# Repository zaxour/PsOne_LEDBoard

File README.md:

# PsOne_LEDBoard
Simple switch board for PsOne LCD LED mods. 

Connects 4 LED's in a 2x2 configuration (2 parallel sets of 2 diodes in series) to the main board's 7.5V rail, which is then controlled by the AV port 5V supply, so that it only turns on when you press the power button on the system.

Parts are indicated on the schematic PDF - BJT gate resistors are 0603 size and the collector resistor is 1210/1206. The LED's I used are also indicated, but are ultimately up to the user. Just make sure to account for diode voltage drop and resize your resistor accordingly.

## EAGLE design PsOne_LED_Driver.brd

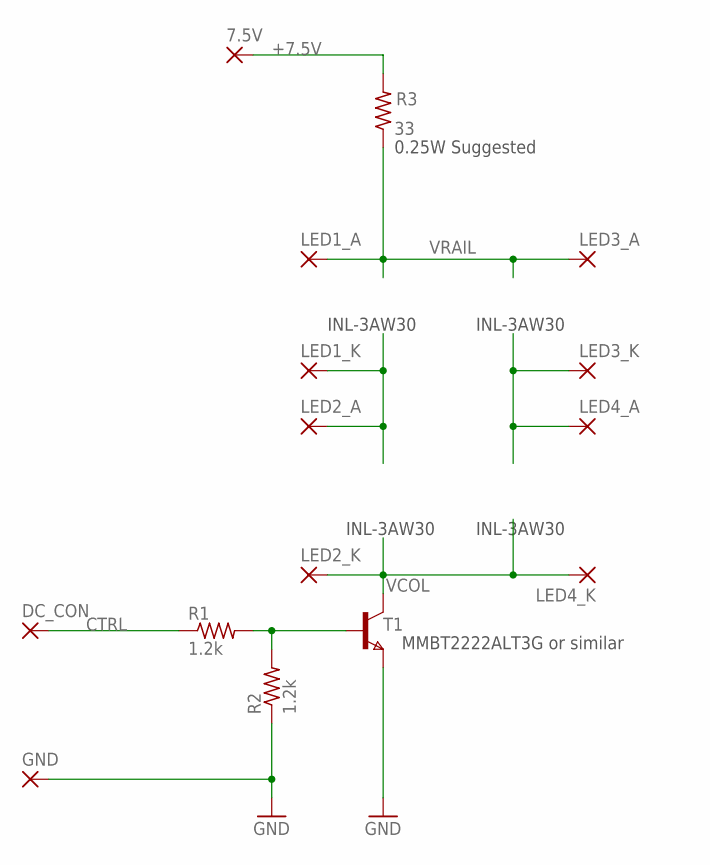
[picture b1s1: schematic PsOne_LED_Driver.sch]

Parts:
7.5V: SMD5; SMD2,54-5,08
DC_CON: SMD5; SMD2,54-5,08
GND: SMD5; SMD2,54-5,08
LED1_A, LED1_K, LED2_A, LED2_K, LED3_A, LED3_K, LED4_A, LED4_K: SMD2; SMD1,27-2,54
R1, R2: 1.2k; R0603
R3: 33; R1206
T1: NPNSOT23; SOT-23

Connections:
+7.5V: 7.5V.1, R3.2
CTRL: DC_CON.1, R1.1
GND: GND.1, R2.1, T1.2 (E)
unnamed: LED3_K.1, LED4_A.1
unnamed: R1.2, R2.2, T1.3 (B)
unnamed: LED1_K.1, LED2_A.1
VCOL: LED2_K.1, LED4_K.1, T1.1 (C)
VRAIL: LED1_A.1, LED3_A.1, R3.1

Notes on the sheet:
MMBT2222ALT3G or similar
0.25W Suggested
INL-3AW30

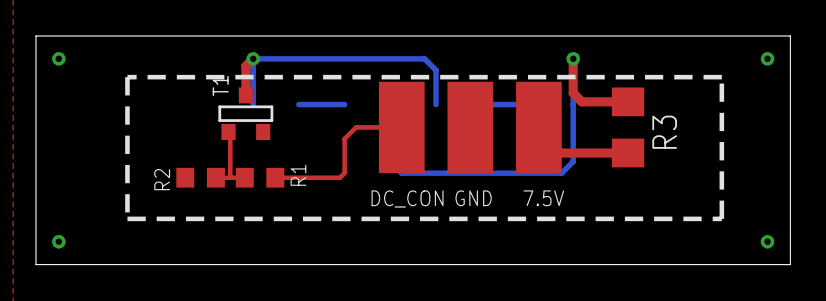
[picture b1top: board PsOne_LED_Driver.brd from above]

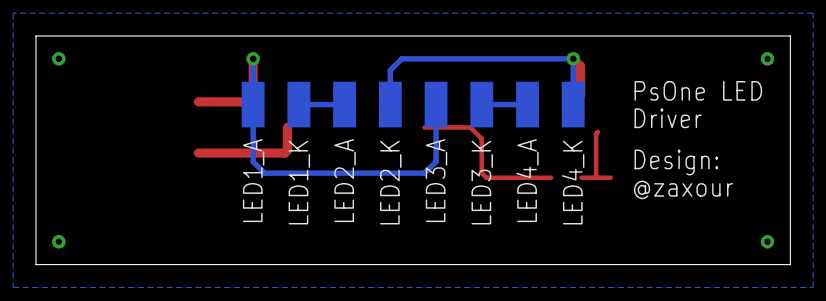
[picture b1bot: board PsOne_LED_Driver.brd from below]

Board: 2 copper layers, 41.9 x 12.7 mm, 15 parts (8 on the bottom side), 8 nets.
